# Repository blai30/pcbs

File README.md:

# pcbs

This is where I keep my PCB designs.

Each board lives in `boards/<board>/`. Boards are designed in KiCad 10 and made by PCBWay.

## Printing at actual size

Paper prints of board outlines (for fit checks against a real board) have to come out 1:1. Measure a known line on the print before trusting it.

The Brother HL-L2305 needs Brother's own driver for this. With Windows' generic Microsoft IPP Class Driver it shrinks every page to about 95%, even with "Actual size" selected and the driver's scaling set to None.

## License

Hardware (KiCad files, fab files, and everything else outside `firmware/` folders) is under the CERN Open Hardware Licence v2, Permissive (CERN-OHL-P-2.0, see `LICENSE`). Firmware in `boards/<board>/firmware/` is under GPL-2.0-or-later (see the `LICENSE` in that folder), the same as QMK.

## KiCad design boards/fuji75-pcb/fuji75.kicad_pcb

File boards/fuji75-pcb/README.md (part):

# Fuji75 PCB

Replacement hotswap PCB for the Sakura Workshop Fuji75, with per-key RGB and an RP2040. It fits the stock case, plate mount, daughterboard, and JST cable.

The layout is the stock Fuji75 hotswap layout with two changes (`reference/keyboard-layout.json`): stepped caps lock, and 1u Alt, Fn, and Ctrl in the bottom right instead of 1.5u Alt and Ctrl. The nav column is Insert, Delete, PgUp, and PgDn.

## KiCad project

Open `fuji75.kicad_pro` in KiCad 10.

- `fuji75.kicad_sch`: root sheet
- `fuji75-key-matrix.kicad_sch` and `fuji75-led-chain.kicad_sch`: generated
- `fuji75-controller.kicad_sch`: USB in, power, the LED power switch, RP2040, flash, clock, boot and reset buttons, SWD pads, and the LED level shifter. Edited by hand
- `fuji75.kicad_pcb`: switches, LEDs, stabilizers, outline, and flex cuts came from the generator. Diodes, LED capacitors, the controller, and all routing were placed and drawn by one-off scripts after that. The board file is the source now
- `layout.json`: the layout with each key's matrix position as its top-left legend (`row,col`, VIA format). Opens in keyboard-layout-editor.com
- `fuji75.kicad_dru`: custom DRC rules for the socket pads at the board edge and the LED cutouts

White solder mask, black silkscreen, and ENIG finish, set in the board stackup (Board Setup, Physical Stackup). Renders only use the colors with `kicad-cli pcb render --use-board-stackup-colors`.

`scripts/generate.py` built the key grid. It's locked now: it rebuilds the schematic and PCB from scratch, so it refuses to run once the PCB has parts it didn't make (the controller) or any tracks. Its `check_holes_inside` and `check_min_web` still work on their own (DRC doesn't check holes crossing an edge or board material thinner than 1 mm).

To run it again on a board without the controller, install kbplacer once with `"C:/Program Files/KiCad/10.0/bin/python.exe" -m pip install --user "kbplacer[schematic]==0.20"`, then run `"C:/Program Files/KiCad/10.0/bin/python.exe" boards/fuji75-pcb/scripts/generate.py` from the repo root (add `--no-flex-cuts` for a solid board).

Footprints in `lib/` are copies from marbastlib (CERN-OHL-P, see `lib/marbastlib-LICENSE`) and KiCad's stock library. The RP2040's QFN-56 pads are 0.17 mm wide instead of the datasheet's 0.20 mm. White solder mask needs at least 0.22 mm between pads (PCBWay), and 0.17 mm leaves 0.23 mm. `LED_MX_6028R` has its pads renumbered to KiCad's SK6812 numbering (1 GND, 2 DIN, 3 VCC, 4 DOUT), which kbplacer expects.

The socket pads on Esc, \`, the nav column, and Right are trimmed to stop 0.3 mm inside the board edge (the socket tab hangs over the edge, like stock). The arrow keys' LED cutouts open into the bottom edge as notches (a closed cutout would leave a 0.09 mm strip, too thin to make). Don't run "Update Footprints from Library" on those switches or the arrow LEDs (LED73 to LED75), it undoes the trim and the notches.

## Controller

The circuit follows Raspberry Pi's minimal RP2040 design (12 MHz crystal, W25Q16JV flash, AP2112K 3.3 V regulator). USB comes in through J1 in the stock spot, then a USBLC6-2SC6 ESD chip and an AO3401A MOSFET that blocks reversed power. The ESD chip's VBUS pin is on the MOSFET's output side (on the input side, a reversed cable shorts through it). R1 and R2 are the RP2040's 27 Ω USB series resistors, next to the chip like in Raspberry Pi's design.

The ESD chip and the MOSFET sit on the bottom behind J1 (the side away from the opening). D+ and D- cross under J1 on the top layer. Only flat tracks sit in front of J1's opening, and the cable plug slides in straight. The RP2040, flash, regulator, and level shifter sit under the spacebar, where there's room for them (the strip by J1 is too narrow on 2 layers). USB runs about 19 cm from J1 to the chip. That's fine at full speed (12 Mbps).

GPIO pin map:

| GPIO | Signal |
| --- | --- |
| 0 | Board ID, tied to GND (v1.1.0) |
| 1 | ROW5 |
| 2 | LED data (through the 74AHCT1G125 to 5 V) |
| 3 | ROW4 |
| 4 to 7 | COL3, COL2, COL1, COL0 |
| 8 to 11 | ROW3, ROW2, ROW1, ROW0 |
| 13 | `LED_FAULT`, U6's fault output (v1.1.0) |
| 14 | `LED_EN`, U6's enable (v1.1.0) |
| 18 to 28 | COL14 down to COL4 |
| 29 | `LED_SENSE`, the LED voltage through a divider (v1.1.0) |

GPIO 12 and 15 to 17 are unused. On v1.0.0, GPIO 0, 13, 14, and 29 are unconnected.

Parts sit on both sides. The crystal, the 12 RP2040 decoupling capacitors, R1 and R2, and the sense divider are on the top side right above the chip (under the spacebar), and so are the boot and reset buttons.

To enter the bootloader, pull the spacebar keycap, hold the boot button through the plate window right of the spacebar switch (a toothpick or tweezers work), and plug in the cable. A board with blank flash goes to the bootloader on its own. The reset button (SW101) sits right of the boot button in the same window. Holding boot and pressing reset enters the bootloader without unplugging. RUN has no external pull-up (the RP2040's internal one holds it high). Keycaps can't reach the buttons, even multi-stem spacebars (they sit below the plate). The plate needs an opening over the buttons. The FR4 plate has its own window for both. On the stock plate, only the boot button sits inside the spacebar cutout. The plate mostly covers the reset button.

SWD pads TP1 to TP5 sit on the bottom about 9 mm south of the RP2040, 2.54 mm apart, for clips or a probe. With the board flipped over to read the bottom silkscreen, left to right: RUN, DIO (SWDIO), CLK (SWCLK), GND, 3V3. That's the reverse of the order in a top view.

## Power

VBUS goes through Q1 (reverse protection) to `VCC`. The controller gets its own 0.3 mm feed from Q1. The LEDs sit behind U6, a TPS2553 load switch with soft-start, enable, and fault output. R5 (21.5 kΩ) sets its current limit to about 1.2 A, above the firmware's LED budget. C119 (1 µF) is on its input and C120 (10 µF) on its output.

U6's output is `LED_5V`. All 82 LEDs and their 100 nF caps are on it. The trunk down the left edge is 1.0 mm (0.5 mm for a short span by a peg hole), and the 0.2 mm row lines branch off it.

R6 (15 kΩ) and R7 (10 kΩ) divide `LED_5V` down to 0.4 for GPIO 29 (ADC). The tap is on the row-4 lane near the controller, far from the feed at the top left. It sees close to the worst drop on the board.

The budget comes from the JST SH connector, rated 1 A per contact (one VBUS pin, one GND pin). The firmware estimates each frame's current and scales the frame down when it's over budget:

- v1.0.0: fixed 800 mA. 950 mA sagged the LED voltage under 4.5 V and turned white orange
- v1.1.0: adaptive, 300 to 950 mA. It lowers the budget when `LED_5V` sags and raises it back slowly

One firmware build runs on both. It reads GPIO 0 at startup (tied to GND on v1.1.0, pulled up internally on v1.0.0) to tell them apart.

## Firmware

QMK with VIA, in `firmware/`. See `firmware/readme.md` for building, flashing, and loading the VIA definition.

- 1000 Hz polling and NKRO
- RGB brightness goes to 255. A current limit in the RGB driver scales each frame to the LED budget (see [Power](#power))
- One build for v1.0.0 and v1.1.0. Each revision has its own VIA definition (caps lock differs)
- USB ID `0x1209`/`0x0001` is pid.codes' test PID until this board gets its own

## Routing

Each layer has one job. Rows and columns never cross on the same layer:

- Top: the columns, straight down between the switches. They cross a flex cut only at a bridge or in the 10 mm strips at the ends
- Bottom: one row line and one LED power line straight through each row of keys, and the LED data chain hopping LED to LED. The LEDs in rows 0, 2, and 4 are turned around, and the chain snakes left-right-left down the board
- Between rows 4 and 5, the columns gather into two buses into the chip
- Ground fill on both sides, stitched together with vias
- No bottom copper within 2.5 mm of a stabilizer screw hole, where the screw heads sit (keepouts in the stabilizer footprints)
- Flex cuts stop at least 4 mm from any stabilizer hole (the stabilizer housing never sits across a cut)

Tracks are 0.2 mm, including the LED power line through each row. The 5 V trunk is 1.0 mm (0.5 mm by one peg hole). The controller's 5 V feed and the 3.3 V lines are 0.3 to 0.5 mm. The USBLC6-2SC6 and button footprints mark the pads that are joined inside the part (jumper pad groups). DRC treats them as connected.

## Plate

`plate/fuji75-plate.kicad_pcb` is an FR4 switch plate for this layout, ordered as a PCB. It shares the PCB's coordinates and lines up with it when overlaid.

`scripts/plate.py` builds it from the stock plate DXF:

- Stock outline and T-shaped gasket tabs
- Stock 14 mm switch cutouts wherever they match a switch on the PCB (70 of 82)
- Stock backspace cutout, copied to Enter and left shift
- A plain 14 mm spacebar switch cutout, and a separate window over the boot and reset buttons, with at least 3 mm of plate between the two
- New cutouts for the rest from the PCB footprints: stepped caps lock, backslash, the bottom row, and the spacebar stabilizers. The multi-layout stock cutouts are gone
- Spacebar stabilizer cutouts the size of the backspace's stabilizer notches (the stock ones were 1.5 mm taller)
- No flex cuts. JLCPCB rejected slots closer than 3 mm to another cutout or the edge, and there's no room for that between keys. Every cutout is at least 3 mm from the next. The only narrower spots are 1.1 to 1.6 mm between the bottom row and the bottom edge, set by the stock outline

`--slots` adds the stock plate's 2 mm vertical slots between keys (plus new ones between the bottom-right 1u keys). `--row-cuts` adds 1 mm cuts between rows with staggered 3 mm bridges (the printed plate's pattern in the 3d-prints repo), stopping 1.5 mm from every cutout and slot. Both leave 1.5 to 2 mm webs, for a fab that allows them.

It also writes `plate/fuji75-plate-foam.dxf` and a 1:1 vector `plate/fuji75-plate-foam.pdf` (for shops that ask for a PDF), the plate foam that sits between the plate and the PCB (3 to 3.5 mm PORON or PE, the gap is about 3.4 mm under the 1.6 mm plate). It follows the PCB outline 0.5 mm in, with:

- A 15 mm hole for each switch (14 mm below the plate, plus room for the clips)
- A hole over each stabilizer housing, clearing both of its PCB holes by 0.75 mm
- A channel for each stabilizer wire between its housings, from 3 mm inside the big PCB holes to past their outer edge (the wire runs under the plate). The spacebar's channel cuts off the foam under the spacebar, so that's two loose pieces that drop in on their own
- One region around the controller parts on top of the PCB under the spacebar, and one around the boot and reset buttons
- Holes closer than 1.9 mm to each other or to the edge merged into one region (thinner foam tears), so the top and side rows open into the edge. Loose islands that leaves (one, by left Ctrl and Win) are cut out too

The script checks that every switch and both buttons sit fully inside a cutout, that the plate is still one piece, and that nothing leaves less than 1 mm of material. Install its libraries once with `"C:/Program Files/KiCad/10.0/bin/python.exe" -m pip install --user ezdxf shapely`, then run `"C:/Program Files/KiCad/10.0/bin/python.exe" boards/fuji75-pcb/scripts/plate.py` from the repo root. Run `fab.py` after it.

## Fab

Run `"C:/Program Files/KiCad/10.0/bin/python.exe" boards/fuji75-pcb/scripts/fab.py` from the repo root. It writes `build/fab/`:

- `fuji75-gerbers.zip`: Gerbers and drill files
- `fuji75-bom.csv`: BOM with manufacturer and LCSC part numbers (every symbol has `MPN` and `LCSC` fields)
- `fuji75-bom-jlcpcb.csv`: the same BOM in JLCPCB's format (Comment, Designator, Footprint, LCSC Part #)
- `fuji75-cpl.csv`: placement for both sides
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
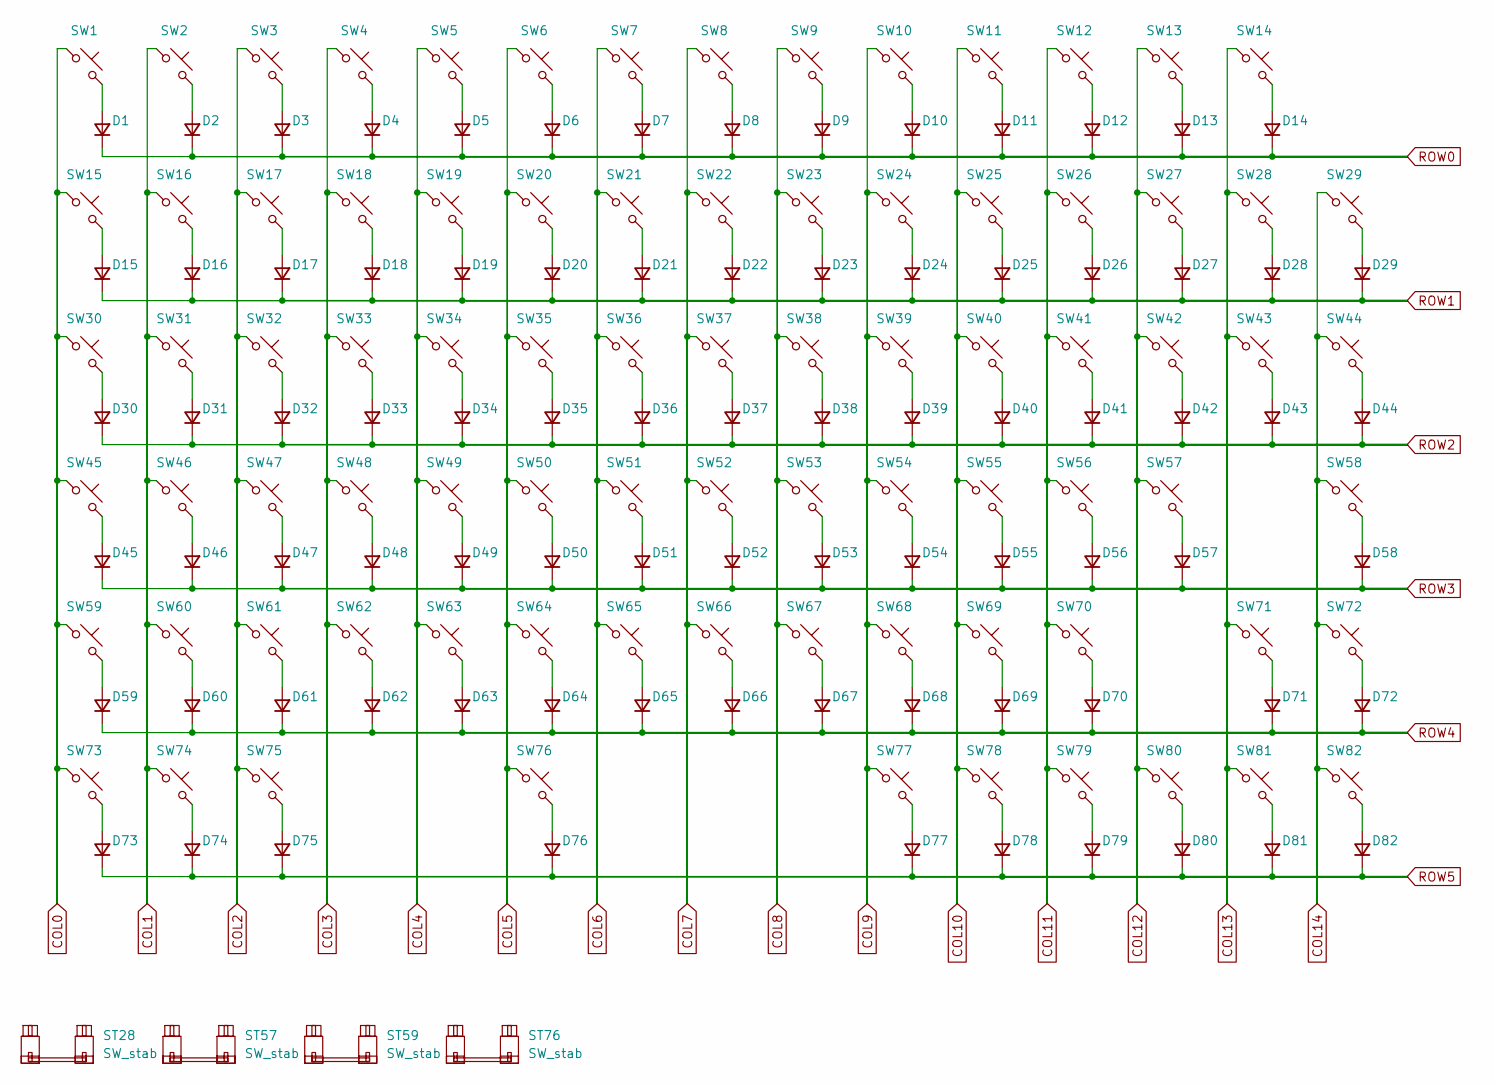
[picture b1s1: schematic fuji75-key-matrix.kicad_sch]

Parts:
D1, D2, D3, D4, D5, D6, D7, D8, D9, D10, D11, D12, D13, D14, D15, D16, D17, D18, D19, D20, D21, D22, D23, D24, D25, D26, D27, D28, D29, D30, D31, D32, D33, D34, D35, D36, D37, D38, D39, D40, D41, D42, D43, D44, D45, D46, D47, D48, D49, D50, D51, D52, D53, D54, D55, D56, D57, D58, D59, D60, D61, D62, D63, D64, D65, D66, D67, D68, D69, D70, D71, D72, D73, D74, D75, D76, D77, D78, D79, D80, D81, D82: D; D_SOD-123; MPN 1N4148W; LCSC C81598
ST28: SW_stab; STAB_MX_2u
ST57, ST59: SW_stab; STAB_MX_2.25u
ST76: SW_stab; STAB_MX_6.25u
SW1, SW2, SW3, SW4, SW5, SW6, SW7, SW8, SW9, SW10, SW11, SW12, SW13, SW14, SW15, SW16, SW17, SW18, SW19, SW20, SW21, SW22, SW23, SW24, SW25, SW26, SW27, SW28, SW29, SW31, SW32, SW33, SW34, SW35, SW36, SW37, SW38, SW39, SW40, SW41, SW42, SW44, SW46, SW47, SW48, SW49, SW50, SW51, SW52, SW53, SW54, SW55, SW56, SW57, SW58, SW59, SW60, SW61, SW62, SW63, SW64, SW65, SW66, SW67, SW68, SW69, SW71, SW72, SW76, SW77, SW78, SW79, SW80, SW81, SW82: SW_Push; SW_MX_HS_CPG151101S11_1u; MPN CPG151101S11; LCSC C2803348
SW30, SW43: SW_Push; SW_MX_HS_CPG151101S11_1.5u; MPN CPG151101S11; LCSC C2803348
SW45, SW70: SW_Push; SW_MX_HS_CPG151101S11_1.75u; MPN CPG151101S11; LCSC C2803348
SW73, SW74, SW75: SW_Push; SW_MX_HS_CPG151101S11_1.25u; MPN CPG151101S11; LCSC C2803348

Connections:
COL0: SW1.1, SW15.1, SW30.1, SW45.1, SW59.1, SW73.1; also elsewhere on the board
COL1: SW2.1, SW16.1, SW31.1, SW46.1, SW60.1, SW74.1; also elsewhere on the board
COL2: SW3.1, SW17.1, SW32.1, SW47.1, SW61.1, SW75.1; also elsewhere on the board
COL3: SW4.1, SW18.1, SW33.1, SW48.1, SW62.1; also elsewhere on the board
COL4: SW5.1, SW19.1, SW34.1, SW49.1, SW63.1; also elsewhere on the board
COL5: SW6.1, SW20.1, SW35.1, SW50.1, SW64.1, SW76.1; also elsewhere on the board
COL6: SW7.1, SW21.1, SW36.1, SW51.1, SW65.1; also elsewhere on the board
COL7: SW8.1, SW22.1, SW37.1, SW52.1, SW66.1; also elsewhere on the board
COL8: SW9.1, SW23.1, SW38.1, SW53.1, SW67.1; also elsewhere on the board
COL9: SW10.1, SW24.1, SW39.1, SW54.1, SW68.1, SW77.1; also elsewhere on the board
COL10: SW11.1, SW25.1, SW40.1, SW55.1, SW69.1, SW78.1; also elsewhere on the board
COL11: SW12.1, SW26.1, SW41.1, SW56.1, SW70.1, SW79.1; also elsewhere on the board
COL12: SW13.1, SW27.1, SW42.1, SW57.1, SW80.1; also elsewhere on the board
COL13: SW14.1, SW28.1, SW43.1, SW71.1, SW81.1; also elsewhere on the board
COL14: SW29.1, SW44.1, SW58.1, SW72.1, SW82.1; also elsewhere on the board
unnamed: D1.2 (A), SW1.2
unnamed: D2.2 (A), SW2.2
unnamed: D3.2 (A), SW3.2
unnamed: D4.2 (A), SW4.2
unnamed: D5.2 (A), SW5.2
unnamed: D6.2 (A), SW6.2
unnamed: D7.2 (A), SW7.2
unnamed: D8.2 (A), SW8.2
unnamed: D9.2 (A), SW9.2
unnamed: D10.2 (A), SW10.2
unnamed: D11.2 (A), SW11.2
unnamed: D12.2 (A), SW12.2
unnamed: D13.2 (A), SW13.2
unnamed: D14.2 (A), SW14.2
unnamed: D15.2 (A), SW15.2
unnamed: D16.2 (A), SW16.2
unnamed: D17.2 (A), SW17.2
unnamed: D18.2 (A), SW18.2
unnamed: D19.2 (A), SW19.2
unnamed: D20.2 (A), SW20.2
unnamed: D21.2 (A), SW21.2
unnamed: D22.2 (A), SW22.2
unnamed: D23.2 (A), SW23.2
unnamed: D24.2 (A), SW24.2
unnamed: D25.2 (A), SW25.2
unnamed: D26.2 (A), SW26.2
unnamed: D27.2 (A), SW27.2
unnamed: D28.2 (A), SW28.2
unnamed: D29.2 (A), SW29.2
unnamed: D30.2 (A), SW30.2
unnamed: D31.2 (A), SW31.2
unnamed: D32.2 (A), SW32.2
unnamed: D33.2 (A), SW33.2
unnamed: D34.2 (A), SW34.2
unnamed: D35.2 (A), SW35.2
unnamed: D36.2 (A), SW36.2
unnamed: D37.2 (A), SW37.2
unnamed: D38.2 (A), SW38.2
unnamed: D39.2 (A), SW39.2
unnamed: D40.2 (A), SW40.2
unnamed: D41.2 (A), SW41.2
unnamed: D42.2 (A), SW42.2
unnamed: D43.2 (A), SW43.2
unnamed: D44.2 (A), SW44.2
unnamed: D45.2 (A), SW45.2
unnamed: D46.2 (A), SW46.2
unnamed: D47.2 (A), SW47.2
unnamed: D48.2 (A), SW48.2
unnamed: D49.2 (A), SW49.2
unnamed: D50.2 (A), SW50.2
unnamed: D51.2 (A), SW51.2
unnamed: D52.2 (A), SW52.2
unnamed: D53.2 (A), SW53.2
unnamed: D54.2 (A), SW54.2
unnamed: D55.2 (A), SW55.2
unnamed: D56.2 (A), SW56.2
unnamed: D57.2 (A), SW57.2
unnamed: D58.2 (A), SW58.2
unnamed: D59.2 (A), SW59.2
unnamed: D60.2 (A), SW60.2
unnamed: D61.2 (A), SW61.2
unnamed: D62.2 (A), SW62.2
unnamed: D63.2 (A), SW63.2
unnamed: D64.2 (A), SW64.2
unnamed: D65.2 (A), SW65.2
unnamed: D66.2 (A), SW66.2
unnamed: D67.2 (A), SW67.2
unnamed: D68.2 (A), SW68.2
unnamed: D69.2 (A), SW69.2
unnamed: D70.2 (A), SW70.2
unnamed: D71.2 (A), SW71.2
unnamed: D72.2 (A), SW72.2
unnamed: D73.2 (A), SW73.2
unnamed: D74.2 (A), SW74.2
unnamed: D75.2 (A), SW75.2
unnamed: D76.2 (A), SW76.2
unnamed: D77.2 (A), SW77.2
unnamed: D78.2 (A), SW78.2
unnamed: D79.2 (A), SW79.2
unnamed: D80.2 (A), SW80.2
unnamed: D81.2 (A), SW81.2
unnamed: D82.2 (A), SW82.2
ROW0: D1.1 (K), D2.1 (K), D3.1 (K), D4.1 (K), D5.1 (K), D6.1 (K), D7.1 (K), D8.1 (K), D9.1 (K), D10.1 (K), D11.1 (K), D12.1 (K), D13.1 (K), D14.1 (K); also elsewhere on the board
ROW1: D15.1 (K), D16.1 (K), D17.1 (K), D18.1 (K), D19.1 (K), D20.1 (K), D21.1 (K), D22.1 (K), D23.1 (K), D24.1 (K), D25.1 (K), D26.1 (K), D27.1 (K), D28.1 (K), D29.1 (K); also elsewhere on the board
ROW2: D30.1 (K), D31.1 (K), D32.1 (K), D33.1 (K), D34.1 (K), D35.1 (K), D36.1 (K), D37.1 (K), D38.1 (K), D39.1 (K), D40.1 (K), D41.1 (K), D42.1 (K), D43.1 (K), D44.1 (K); also elsewhere on the board
ROW3: D45.1 (K), D46.1 (K), D47.1 (K), D48.1 (K), D49.1 (K), D50.1 (K), D51.1 (K), D52.1 (K), D53.1 (K), D54.1 (K), D55.1 (K), D56.1 (K), D57.1 (K), D58.1 (K); also elsewhere on the board
ROW4: D59.1 (K), D60.1 (K), D61.1 (K), D62.1 (K), D63.1 (K), D64.1 (K), D65.1 (K), D66.1 (K), D67.1 (K), D68.1 (K), D69.1 (K), D70.1 (K), D71.1 (K), D72.1 (K); also elsewhere on the board
ROW5: D73.1 (K), D74.1 (K), D75.1 (K), D76.1 (K), D77.1 (K), D78.1 (K), D79.1 (K), D80.1 (K), D81.1 (K), D82.1 (K); also elsewhere on the board

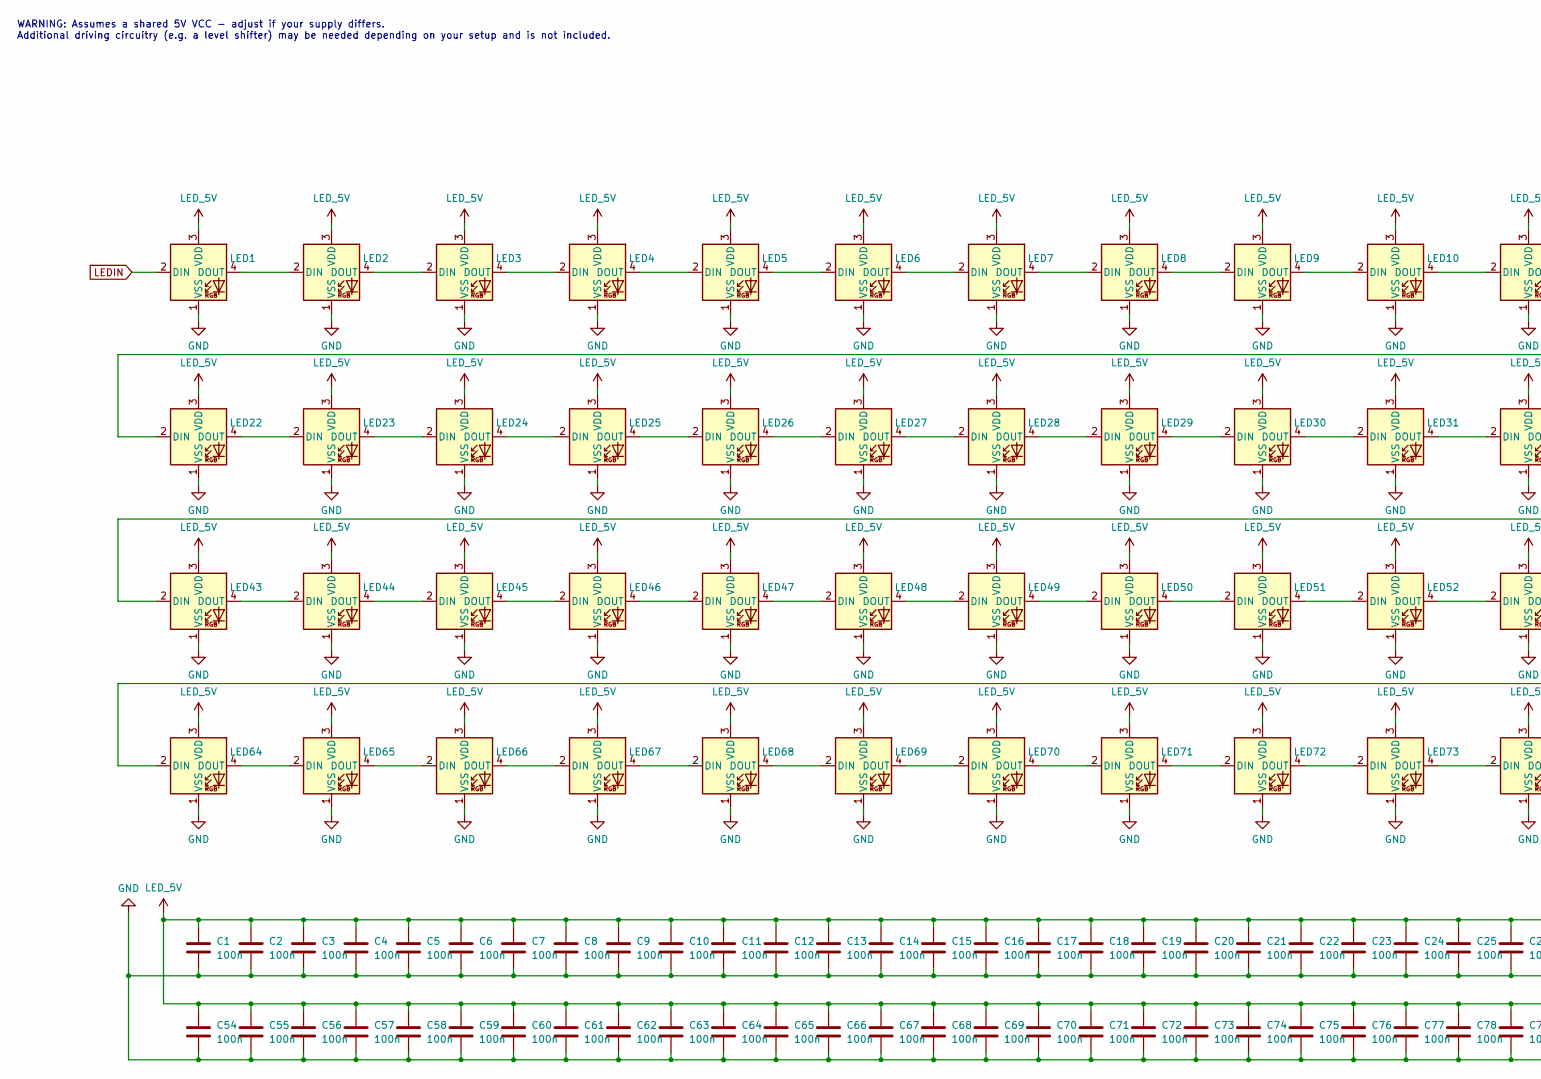
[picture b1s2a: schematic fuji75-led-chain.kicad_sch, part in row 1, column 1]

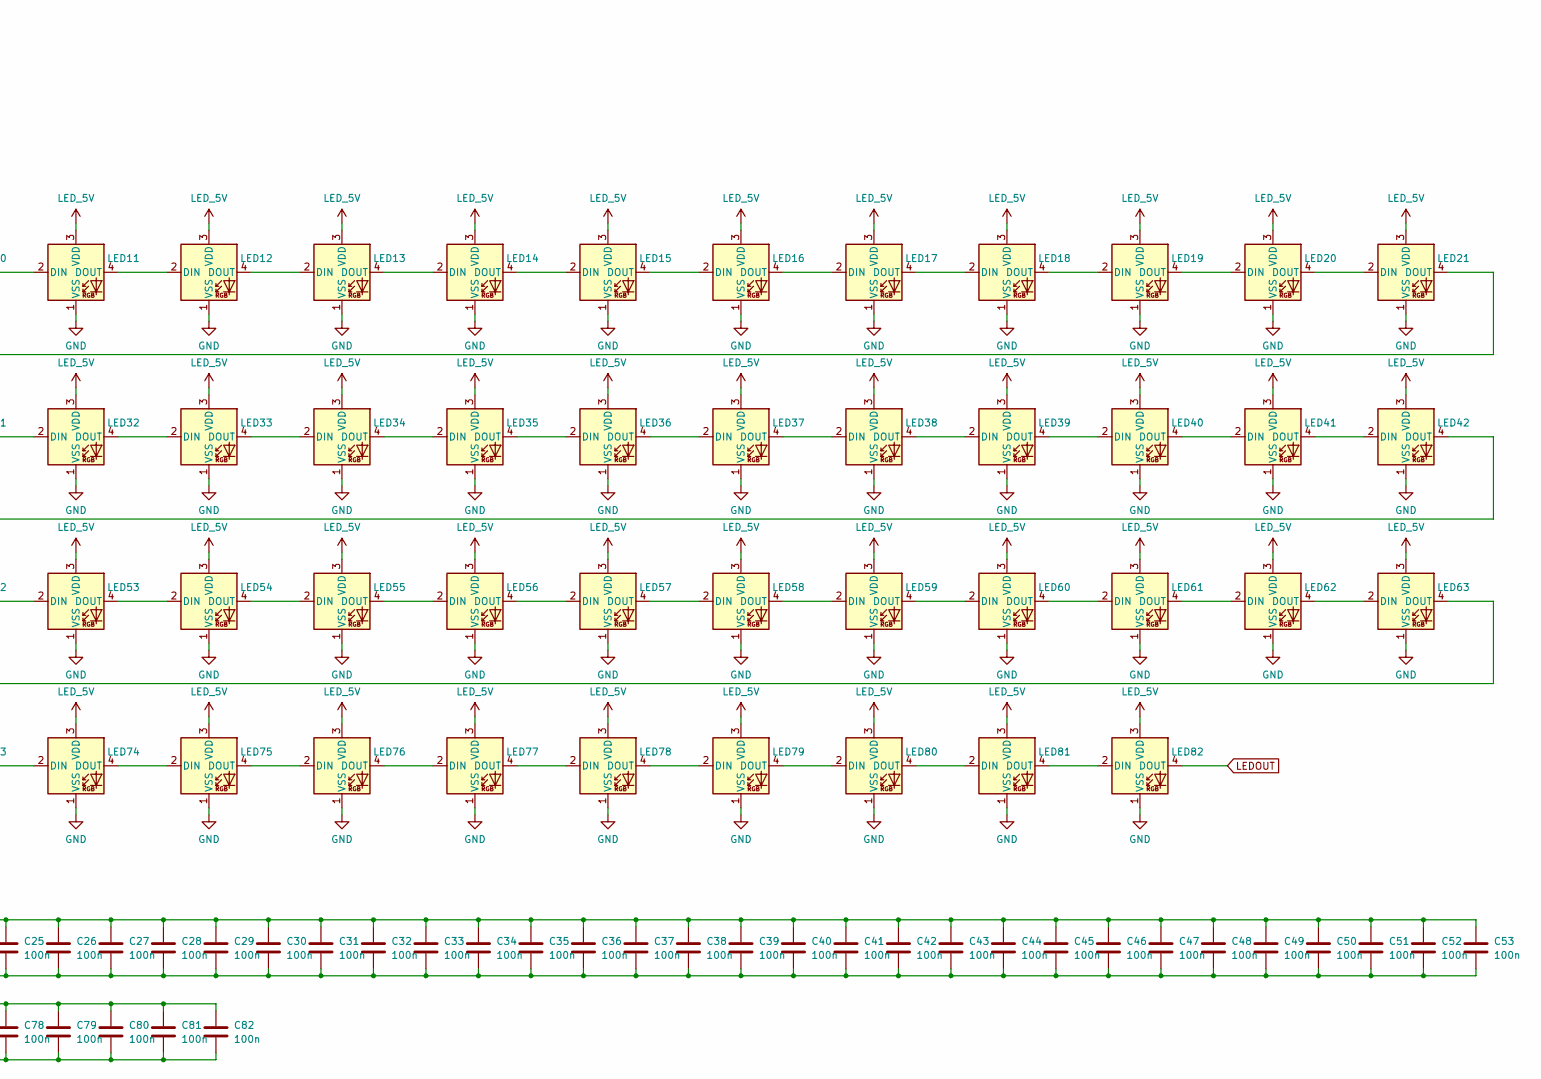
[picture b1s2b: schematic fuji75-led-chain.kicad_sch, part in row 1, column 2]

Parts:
C1, C2, C3, C4, C5, C6, C7, C8, C9, C10, C11, C12, C13, C14, C15, C16, C17, C18, C19, C20, C21, C22, C23, C24, C25, C26, C27, C28, C29, C30, C31, C32, C33, C34, C35, C36, C37, C38, C39, C40, C41, C42, C43, C44, C45, C46, C47, C48, C49, C50, C51, C52, C53, C54, C55, C56, C57, C58, C59, C60, C61, C62, C63, C64, C65, C66, C67, C68, C69, C70, C71, C72, C73, C74, C75, C76, C77, C78, C79, C80, C81, C82: 100n; C_0402_1005Metric; MPN CL05B104KO5NNNC; LCSC C1525
LED1, LED2, LED3, LED4, LED5, LED6, LED7, LED8, LED9, LED10, LED11, LED12, LED13, LED14, LED15, LED16, LED17, LED18, LED19, LED20, LED21, LED22, LED23, LED24, LED25, LED26, LED27, LED28, LED29, LED30, LED31, LED32, LED33, LED34, LED35, LED36, LED37, LED38, LED39, LED40, LED41, LED42, LED43, LED44, LED45, LED46, LED47, LED48, LED49, LED50, LED51, LED52, LED53, LED54, LED55, LED56, LED57, LED58, LED59, LED60, LED61, LED62, LED63, LED64, LED65, LED66, LED67, LED68, LED69, LED70, LED71, LED72, LED73, LED74, LED75, LED76, LED77, LED78, LED79, LED80, LED81, LED82: SK6812MINI-E; LED_MX_6028R; MPN SK6812MINI-E; LCSC C5149201

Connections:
GND: C1.2, C2.2, C3.2, C4.2, C5.2, C6.2, C7.2, C8.2, C9.2, C10.2, C11.2, C12.2, C13.2, C14.2, C15.2, C16.2, C17.2, C18.2, C19.2, C20.2, C21.2, C22.2, C23.2, C24.2, C25.2, C26.2, C27.2, C28.2, C29.2, C30.2, C31.2, C32.2, C33.2, C34.2, C35.2, C36.2, C37.2, C38.2, C39.2, C40.2, C41.2, C42.2, C43.2, C44.2, C45.2, C46.2, C47.2, C48.2, C49.2, C50.2, C51.2, C52.2, C53.2, C54.2, C55.2, C56.2, C57.2, C58.2, C59.2, C60.2, C61.2, C62.2, C63.2, C64.2, C65.2, C66.2, C67.2, C68.2, C69.2, C70.2, C71.2, C72.2, C73.2, C74.2, C75.2, C76.2, C77.2, C78.2, C79.2, C80.2, C81.2, C82.2, LED1.1 (VSS), LED2.1 (VSS), LED3.1 (VSS), LED4.1 (VSS), LED5.1 (VSS), LED6.1 (VSS), LED7.1 (VSS), LED8.1 (VSS), LED9.1 (VSS), LED10.1 (VSS), LED11.1 (VSS), LED12.1 (VSS), LED13.1 (VSS), LED14.1 (VSS), LED15.1 (VSS), LED16.1 (VSS), LED17.1 (VSS), LED18.1 (VSS), LED19.1 (VSS), LED20.1 (VSS), LED21.1 (VSS), LED22.1 (VSS), LED23.1 (VSS), LED24.1 (VSS), LED25.1 (VSS), LED26.1 (VSS), LED27.1 (VSS), LED28.1 (VSS), LED29.1 (VSS), LED30.1 (VSS), LED31.1 (VSS), LED32.1 (VSS), LED33.1 (VSS), LED34.1 (VSS), LED35.1 (VSS), LED36.1 (VSS), LED37.1 (VSS), LED38.1 (VSS), LED39.1 (VSS), LED40.1 (VSS), LED41.1 (VSS), LED42.1 (VSS), LED43.1 (VSS), LED44.1 (VSS), LED45.1 (VSS), LED46.1 (VSS), LED47.1 (VSS), LED48.1 (VSS), LED49.1 (VSS), LED50.1 (VSS), LED51.1 (VSS), LED52.1 (VSS), LED53.1 (VSS), LED54.1 (VSS), LED55.1 (VSS), LED56.1 (VSS), LED57.1 (VSS), LED58.1 (VSS), LED59.1 (VSS), LED60.1 (VSS), LED61.1 (VSS), LED62.1 (VSS), LED63.1 (VSS), LED64.1 (VSS), LED65.1 (VSS), LED66.1 (VSS), LED67.1 (VSS), LED68.1 (VSS), LED69.1 (VSS), LED70.1 (VSS), LED71.1 (VSS), LED72.1 (VSS), LED73.1 (VSS), LED74.1 (VSS), LED75.1 (VSS), LED76.1 (VSS), LED77.1 (VSS), LED78.1 (VSS), LED79.1 (VSS), LED80.1 (VSS), LED81.1 (VSS), LED82.1 (VSS); also elsewhere on the board
LEDIN: LED1.2 (DIN); also elsewhere on the board
LEDOUT: LED82.4 (DOUT)
LED_5V: C1.1, C2.1, C3.1, C4.1, C5.1, C6.1, C7.1, C8.1, C9.1, C10.1, C11.1, C12.1, C13.1, C14.1, C15.1, C16.1, C17.1, C18.1, C19.1, C20.1, C21.1, C22.1, C23.1, C24.1, C25.1, C26.1, C27.1, C28.1, C29.1, C30.1, C31.1, C32.1, C33.1, C34.1, C35.1, C36.1, C37.1, C38.1, C39.1, C40.1, C41.1, C42.1, C43.1, C44.1, C45.1, C46.1, C47.1, C48.1, C49.1, C50.1, C51.1, C52.1, C53.1, C54.1, C55.1, C56.1, C57.1, C58.1, C59.1, C60.1, C61.1, C62.1, C63.1, C64.1, C65.1, C66.1, C67.1, C68.1, C69.1, C70.1, C71.1, C72.1, C73.1, C74.1, C75.1, C76.1, C77.1, C78.1, C79.1, C80.1, C81.1, C82.1, LED1.3 (VDD), LED2.3 (VDD), LED3.3 (VDD), LED4.3 (VDD), LED5.3 (VDD), LED6.3 (VDD), LED7.3 (VDD), LED8.3 (VDD), LED9.3 (VDD), LED10.3 (VDD), LED11.3 (VDD), LED12.3 (VDD), LED13.3 (VDD), LED14.3 (VDD), LED15.3 (VDD), LED16.3 (VDD), LED17.3 (VDD), LED18.3 (VDD), LED19.3 (VDD), LED20.3 (VDD), LED21.3 (VDD), LED22.3 (VDD), LED23.3 (VDD), LED24.3 (VDD), LED25.3 (VDD), LED26.3 (VDD), LED27.3 (VDD), LED28.3 (VDD), LED29.3 (VDD), LED30.3 (VDD), LED31.3 (VDD), LED32.3 (VDD), LED33.3 (VDD), LED34.3 (VDD), LED35.3 (VDD), LED36.3 (VDD), LED37.3 (VDD), LED38.3 (VDD), LED39.3 (VDD), LED40.3 (VDD), LED41.3 (VDD), LED42.3 (VDD), LED43.3 (VDD), LED44.3 (VDD), LED45.3 (VDD), LED46.3 (VDD), LED47.3 (VDD), LED48.3 (VDD), LED49.3 (VDD), LED50.3 (VDD), LED51.3 (VDD), LED52.3 (VDD), LED53.3 (VDD), LED54.3 (VDD), LED55.3 (VDD), LED56.3 (VDD), LED57.3 (VDD), LED58.3 (VDD), LED59.3 (VDD), LED60.3 (VDD), LED61.3 (VDD), LED62.3 (VDD), LED63.3 (VDD), LED64.3 (VDD), LED65.3 (VDD), LED66.3 (VDD), LED67.3 (VDD), LED68.3 (VDD), LED69.3 (VDD), LED70.3 (VDD), LED71.3 (VDD), LED72.3 (VDD), LED73.3 (VDD), LED74.3 (VDD), LED75.3 (VDD), LED76.3 (VDD), LED77.3 (VDD), LED78.3 (VDD), LED79.3 (VDD), LED80.3 (VDD), LED81.3 (VDD), LED82.3 (VDD); also elsewhere on the board
unnamed: LED1.4 (DOUT), LED2.2 (DIN)
unnamed: LED2.4 (DOUT), LED3.2 (DIN)
unnamed: LED3.4 (DOUT), LED4.2 (DIN)
unnamed: LED4.4 (DOUT), LED5.2 (DIN)
unnamed: LED5.4 (DOUT), LED6.2 (DIN)
unnamed: LED6.4 (DOUT), LED7.2 (DIN)
unnamed: LED7.4 (DOUT), LED8.2 (DIN)
unnamed: LED8.4 (DOUT), LED9.2 (DIN)
unnamed: LED9.4 (DOUT), LED10.2 (DIN)
unnamed: LED10.4 (DOUT), LED11.2 (DIN)
unnamed: LED11.4 (DOUT), LED12.2 (DIN)
unnamed: LED12.4 (DOUT), LED13.2 (DIN)
unnamed: LED13.4 (DOUT), LED14.2 (DIN)
unnamed: LED14.4 (DOUT), LED15.2 (DIN)
unnamed: LED15.4 (DOUT), LED16.2 (DIN)
unnamed: LED16.4 (DOUT), LED17.2 (DIN)
unnamed: LED17.4 (DOUT), LED18.2 (DIN)
unnamed: LED18.4 (DOUT), LED19.2 (DIN)
unnamed: LED19.4 (DOUT), LED20.2 (DIN)
unnamed: LED20.4 (DOUT), LED21.2 (DIN)
unnamed: LED21.4 (DOUT), LED22.2 (DIN)
unnamed: LED22.4 (DOUT), LED23.2 (DIN)
unnamed: LED23.4 (DOUT), LED24.2 (DIN)
unnamed: LED24.4 (DOUT), LED25.2 (DIN)
unnamed: LED25.4 (DOUT), LED26.2 (DIN)
unnamed: LED26.4 (DOUT), LED27.2 (DIN)
unnamed: LED27.4 (DOUT), LED28.2 (DIN)
unnamed: LED28.4 (DOUT), LED29.2 (DIN)
unnamed: LED29.4 (DOUT), LED30.2 (DIN)
unnamed: LED30.4 (DOUT), LED31.2 (DIN)
unnamed: LED31.4 (DOUT), LED32.2 (DIN)
unnamed: LED32.4 (DOUT), LED33.2 (DIN)
unnamed: LED33.4 (DOUT), LED34.2 (DIN)
unnamed: LED34.4 (DOUT), LED35.2 (DIN)
unnamed: LED35.4 (DOUT), LED36.2 (DIN)
unnamed: LED36.4 (DOUT), LED37.2 (DIN)
unnamed: LED37.4 (DOUT), LED38.2 (DIN)
unnamed: LED38.4 (DOUT), LED39.2 (DIN)
unnamed: LED39.4 (DOUT), LED40.2 (DIN)
unnamed: LED40.4 (DOUT), LED41.2 (DIN)
unnamed: LED41.4 (DOUT), LED42.2 (DIN)
unnamed: LED42.4 (DOUT), LED43.2 (DIN)
unnamed: LED43.4 (DOUT), LED44.2 (DIN)
unnamed: LED44.4 (DOUT), LED45.2 (DIN)
unnamed: LED45.4 (DOUT), LED46.2 (DIN)
unnamed: LED46.4 (DOUT), LED47.2 (DIN)
unnamed: LED47.4 (DOUT), LED48.2 (DIN)
unnamed: LED48.4 (DOUT), LED49.2 (DIN)
unnamed: LED49.4 (DOUT), LED50.2 (DIN)
unnamed: LED50.4 (DOUT), LED51.2 (DIN)
unnamed: LED51.4 (DOUT), LED52.2 (DIN)
unnamed: LED52.4 (DOUT), LED53.2 (DIN)
unnamed: LED53.4 (DOUT), LED54.2 (DIN)
unnamed: LED54.4 (DOUT), LED55.2 (DIN)
unnamed: LED55.4 (DOUT), LED56.2 (DIN)
unnamed: LED56.4 (DOUT), LED57.2 (DIN)
unnamed: LED57.4 (DOUT), LED58.2 (DIN)
unnamed: LED58.4 (DOUT), LED59.2 (DIN)
unnamed: LED59.4 (DOUT), LED60.2 (DIN)
unnamed: LED60.4 (DOUT), LED61.2 (DIN)
unnamed: LED61.4 (DOUT), LED62.2 (DIN)
unnamed: LED62.4 (DOUT), LED63.2 (DIN)
unnamed: LED63.4 (DOUT), LED64.2 (DIN)
unnamed: LED64.4 (DOUT), LED65.2 (DIN)
unnamed: LED65.4 (DOUT), LED66.2 (DIN)
unnamed: LED66.4 (DOUT), LED67.2 (DIN)
unnamed: LED67.4 (DOUT), LED68.2 (DIN)
unnamed: LED68.4 (DOUT), LED69.2 (DIN)
unnamed: LED69.4 (DOUT), LED70.2 (DIN)
unnamed: LED70.4 (DOUT), LED71.2 (DIN)
unnamed: LED71.4 (DOUT), LED72.2 (DIN)
unnamed: LED72.4 (DOUT), LED73.2 (DIN)
unnamed: LED73.4 (DOUT), LED74.2 (DIN)
unnamed: LED74.4 (DOUT), LED75.2 (DIN)
unnamed: LED75.4 (DOUT), LED76.2 (DIN)
unnamed: LED76.4 (DOUT), LED77.2 (DIN)
unnamed: LED77.4 (DOUT), LED78.2 (DIN)
unnamed: LED78.4 (DOUT), LED79.2 (DIN)
unnamed: LED79.4 (DOUT), LED80.2 (DIN)
unnamed: LED80.4 (DOUT), LED81.2 (DIN)
unnamed: LED81.4 (DOUT), LED82.2 (DIN)

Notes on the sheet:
WARNING: Assumes a shared 5V VCC - adjust if your supply differs. Additional driving circuitry (e.g. a level shifter) may be needed depending on your setup and is not included.

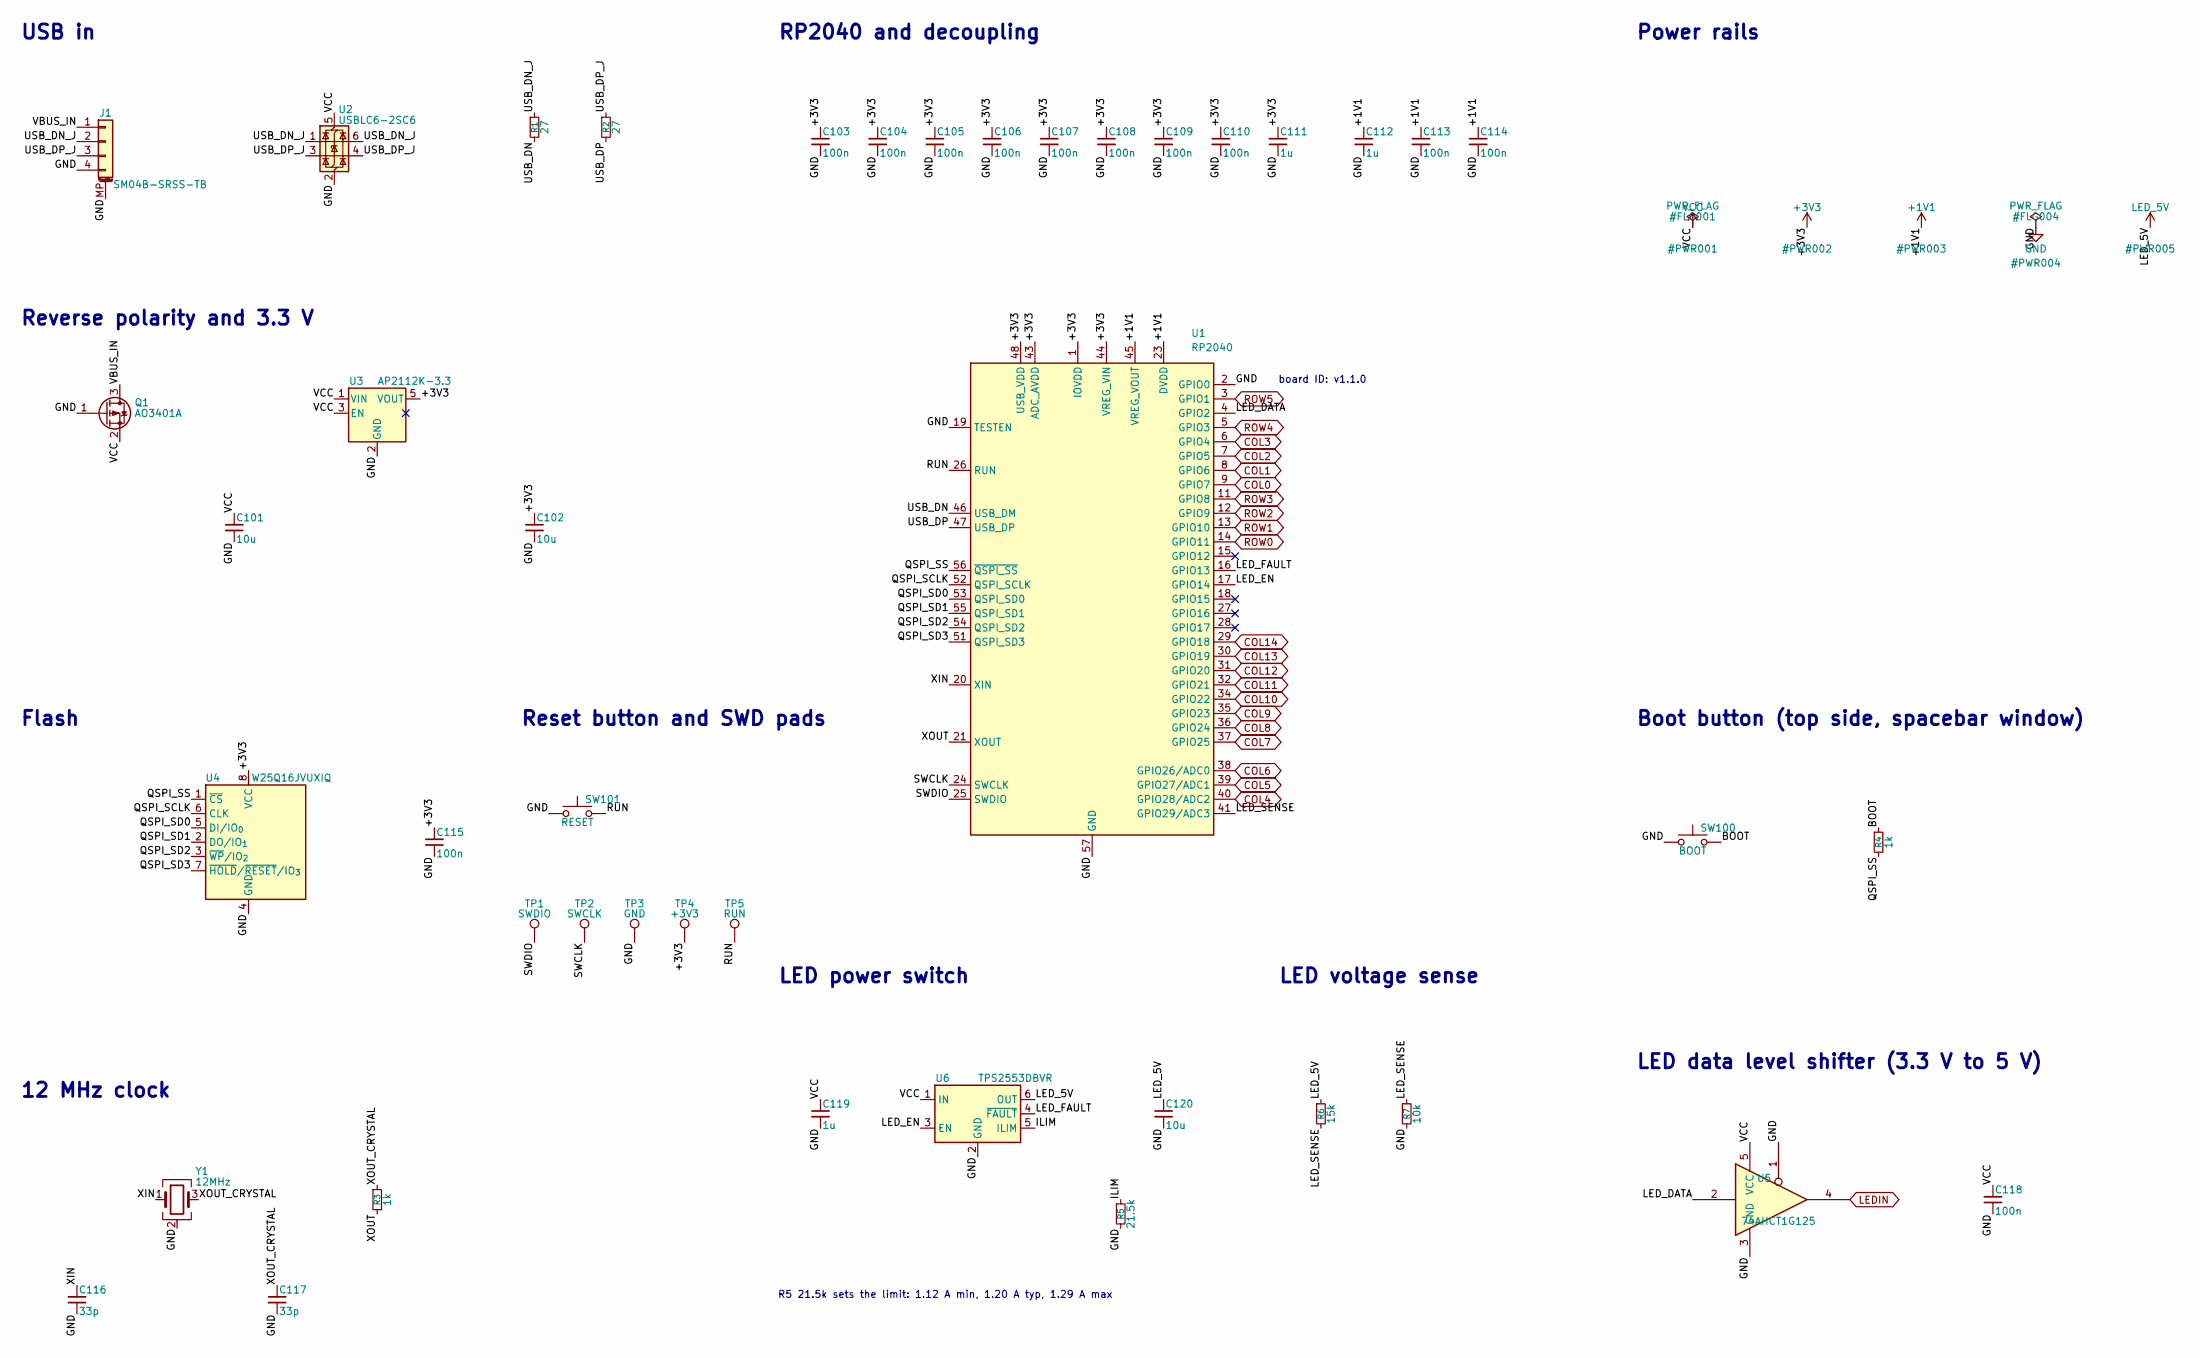
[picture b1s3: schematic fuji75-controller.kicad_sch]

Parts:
C101, C102, C120: 10u; C_0603_1608Metric; MPN CL10A106KP8NNNC; LCSC C19702
C103, C104, C105, C106, C107, C108, C109, C110, C113, C114, C115, C118: 100n; C_0402_1005Metric; MPN CL05B104KO5NNNC; LCSC C1525
C111, C112, C119: 1u; C_0402_1005Metric; MPN CL05A105KA5NQNC; LCSC C52923
C116, C117: 33p; C_0402_1005Metric; MPN 0402CG330J500NT; LCSC C1562
J1: SM04B-SRSS-TB; JST_SH_SM04B-SRSS-TB_1x04-1MP_P1.00mm_Horizontal; MPN SM04B-SRSS-TB(LF)(SN); LCSC C160404
Q1: AO3401A; SOT-23; MPN AO3401A; LCSC C15127
R1, R2: 27; R_0402_1005Metric; MPN 0402WGF270JTCE; LCSC C25100
R3, R4: 1k; R_0402_1005Metric; MPN 0402WGF1001TCE; LCSC C11702
R5: 21.5k; R_0402_1005Metric; MPN 0402WGF2152TCE; LCSC C25872
R6: 15k; R_0402_1005Metric; MPN 0402WGF1502TCE; LCSC C25756
R7: 10k; R_0402_1005Metric; MPN 0402WGF1002TCE; LCSC C25744
SW100: BOOT; SW_Push_1P1T_XKB_TS-1187A; MPN TS-1187A-B-A-B; LCSC C318884
SW101: RESET; SW_Push_1P1T_XKB_TS-1187A; MPN TS-1187A-B-A-B; LCSC C318884
TP1: SWDIO; TestPoint_Pad_D1.0mm
TP2: SWCLK; TestPoint_Pad_D1.0mm
TP3: GND; TestPoint_Pad_D1.0mm
TP4: +3V3; TestPoint_Pad_D1.0mm
TP5: RUN; TestPoint_Pad_D1.0mm
U1: RP2040; QFN-56-1EP_7x7mm_P0.4mm_EP3.2x3.2mm; MPN RP2040; LCSC C2040
U2: USBLC6-2SC6; SOT-23-6; MPN USBLC6-2SC6; LCSC C7519
U3: AP2112K-3.3; SOT-23-5; MPN AP2112K-3.3TRG1; LCSC C51118
U4: W25Q16JVUXIQ; Winbond_USON-8-1EP_3x2mm_P0.5mm_EP0.2x1.6mm; MPN W25Q16JVUXIQ; LCSC C2843335
U5: 74AHCT1G125; SOT-23-5; MPN SN74AHCT1G125DBVR; LCSC C7484
U6: TPS2553DBVR; SOT-23-6_NoJumpers; MPN TPS2553DBVR; LCSC C55266
Y1: 12MHz; Crystal_SMD_3225-4Pin_3.2x2.5mm; MPN X322512MSB4SI; LCSC C9002

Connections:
+1V1: C112.1, C113.1, C114.1, U1.23 (DVDD), U1.45 (VREG_VOUT), U1.50 (DVDD)
+3V3: C102.1, C103.1, C104.1, C105.1, C106.1, C107.1, C108.1, C109.1, C110.1, C111.1, C115.1, TP4.1, U1.1 (IOVDD), U1.10 (IOVDD), U1.22 (IOVDD), U1.33 (IOVDD), U1.42 (IOVDD), U1.43 (ADC_AVDD), U1.44 (VREG_VIN), U1.48 (USB_VDD), U1.49 (IOVDD), U3.5 (VOUT), U4.8 (VCC)
/Controller/BOOT: R4.1, SW100.2
/Controller/ILIM: R5.1, U6.5 (ILIM)
/Controller/LED_DATA: U1.4 (GPIO2), U5.2
/Controller/LED_EN: U1.17 (GPIO14), U6.3 (EN)
/Controller/LED_FAULT: U1.16 (GPIO13), U6.4 (~FAULT)
/Controller/LED_SENSE: R6.2, R7.1, U1.41 (GPIO29/ADC3)
/Controller/QSPI_SCLK: U1.52 (QSPI_SCLK), U4.6 (CLK)
/Controller/QSPI_SD0: U1.53 (QSPI_SD0), U4.5 (DI/IO_{0})
/Controller/QSPI_SD1: U1.55 (QSPI_SD1), U4.2 (DO/IO_{1})
/Controller/QSPI_SD2: U1.54 (QSPI_SD2), U4.3 (~WP/IO_{2})
/Controller/QSPI_SD3: U1.51 (QSPI_SD3), U4.7 (~HOLD/~RESET/IO_{3})
/Controller/QSPI_SS: R4.2, U1.56 (~QSPI_SS), U4.1 (~CS)
/Controller/RUN: SW101.2, TP5.1, U1.26 (RUN)
/Controller/SWCLK: TP2.1, U1.24 (SWCLK)
/Controller/SWDIO: TP1.1, U1.25 (SWDIO)
/Controller/USB_DN: R1.2, U1.46 (USB_DM)
/Controller/USB_DN_J: J1.2, R1.1, U2.1 (I/O1), U2.6 (I/O1)
/Controller/USB_DP: R2.2, U1.47 (USB_DP)
/Controller/USB_DP_J: J1.3, R2.1, U2.3 (I/O2), U2.4 (I/O2)
/Controller/VBUS_IN: J1.1, Q1.3 (D)
/Controller/XIN: C116.1, U1.20 (XIN), Y1.1
/Controller/XOUT: R3.2, U1.21 (XOUT)
/Controller/XOUT_CRYSTAL: C117.1, R3.1, Y1.3
COL0: U1.9 (GPIO7); also elsewhere on the board
COL1: U1.8 (GPIO6); also elsewhere on the board
COL2: U1.7 (GPIO5); also elsewhere on the board
COL3: U1.6 (GPIO4); also elsewhere on the board
COL4: U1.40 (GPIO28/ADC2); also elsewhere on the board
COL5: U1.39 (GPIO27/ADC1); also elsewhere on the board
COL6: U1.38 (GPIO26/ADC0); also elsewhere on the board
COL7: U1.37 (GPIO25); also elsewhere on the board
COL8: U1.36 (GPIO24); also elsewhere on the board
COL9: U1.35 (GPIO23); also elsewhere on the board
COL10: U1.34 (GPIO22); also elsewhere on the board
COL11: U1.32 (GPIO21); also elsewhere on the board
COL12: U1.31 (GPIO20); also elsewhere on the board
COL13: U1.30 (GPIO19); also elsewhere on the board
COL14: U1.29 (GPIO18); also elsewhere on the board
GND: C101.2, C102.2, C103.2, C104.2, C105.2, C106.2, C107.2, C108.2, C109.2, C110.2, C111.2, C112.2, C113.2, C114.2, C115.2, C116.2, C117.2, C118.2, C119.2, C120.2, J1.4, J1.MP (MountPin), Q1.1 (G), R5.2, R7.2, SW100.1, SW101.1, TP3.1, U1.2 (GPIO0), U1.19 (TESTEN), U1.57 (GND), U2.2 (GND), U3.2 (GND), U4.4 (GND), U5.1, U5.3 (GND), U6.2 (GND), Y1.2 (G), Y1.4 (G); also elsewhere on the board
LEDIN: U5.4; also elsewhere on the board
LED_5V: C120.1, R6.1, U6.6 (OUT); also elsewhere on the board
ROW0: U1.14 (GPIO11); also elsewhere on the board
ROW1: U1.13 (GPIO10); also elsewhere on the board
ROW2: U1.12 (GPIO9); also elsewhere on the board
ROW3: U1.11 (GPIO8); also elsewhere on the board
ROW4: U1.5 (GPIO3); also elsewhere on the board
ROW5: U1.3 (GPIO1); also elsewhere on the board
VCC: C101.1, C118.1, C119.1, Q1.2 (S), U2.5 (VBUS), U3.1 (VIN), U3.3 (EN), U5.5 (VCC), U6.1 (IN)

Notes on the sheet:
USB in
Reverse polarity and 3.3 V
RP2040 and decoupling
Flash
12 MHz clock
Power rails
Boot button (top side, spacebar window)
LED data level shifter (3.3 V to 5 V)
LED power switch
LED voltage sense
Reset button and SWD pads
R5 21.5k sets the limit: 1.12 A min, 1.20 A typ, 1.29 A max
board ID: v1.1.0

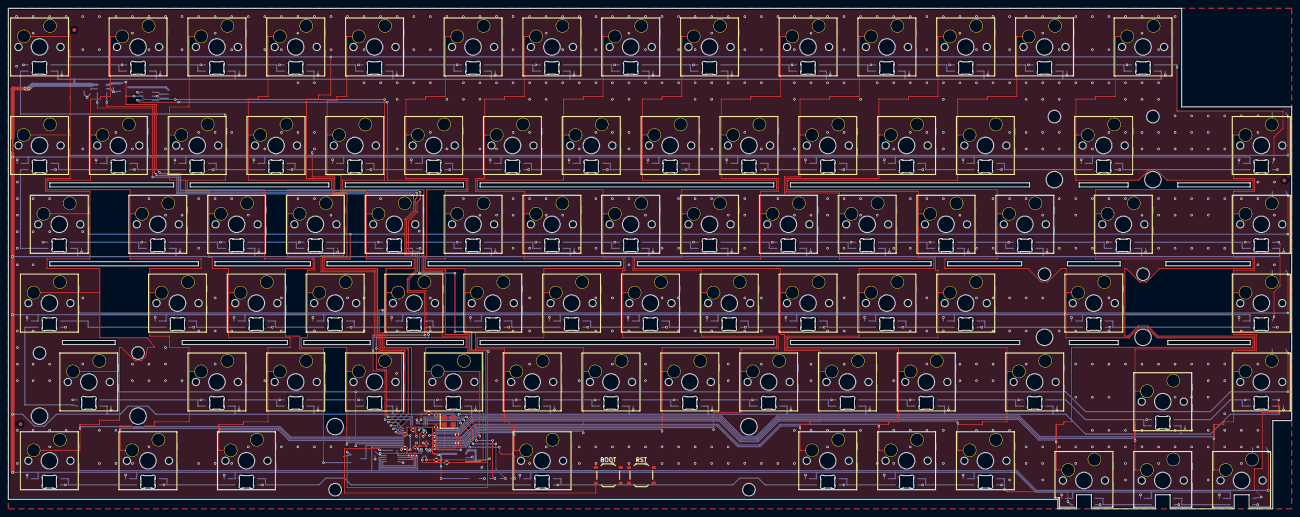
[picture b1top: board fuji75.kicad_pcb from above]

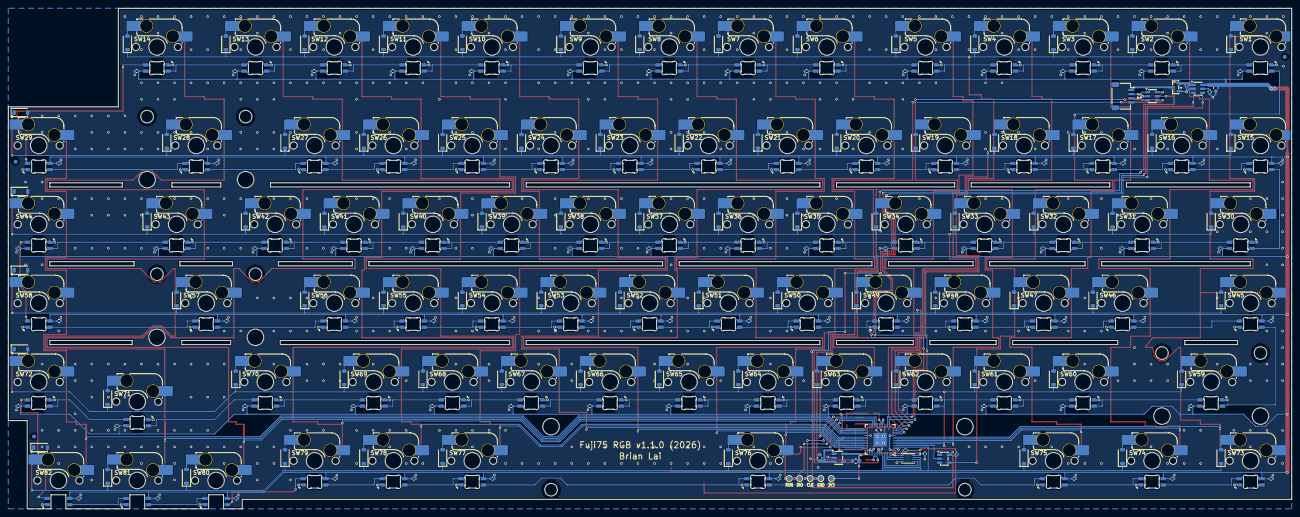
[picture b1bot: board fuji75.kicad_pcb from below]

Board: 2 copper layers, 310.1 x 120.9 mm, 381 parts (352 on the bottom side), 213 nets.

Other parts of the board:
FID1, FID2, FID3, FID4, FID5, FID6: Fiducial_1mm_Mask2mm

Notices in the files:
boards/fuji75-pcb/README.md:
The board is under CERN-OHL-P-2.0 (repo root `LICENSE`). The footprints in `lib/` are marbastlib's, under the same license. The firmware in `firmware/` is under GPL-2.0-or-later.
